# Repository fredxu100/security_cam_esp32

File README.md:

# Portable ESP32-CAM Security System
Low-cost, portable PIR-activated security device that detects motion, records video, and warns intruders.

**PROJECT FEATURES**
- Motion detection
- Camera capture/logging
- Local sound alarm
- Battery powered/portable

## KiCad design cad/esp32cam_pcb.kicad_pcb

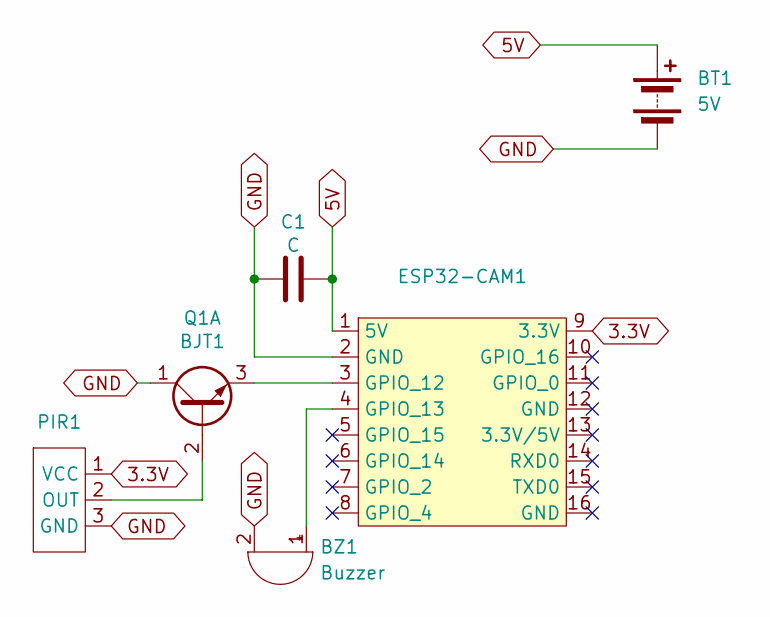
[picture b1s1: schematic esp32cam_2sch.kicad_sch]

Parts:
BT1: 5V; Banana_Jack_2Pin
BZ1: Buzzer; Buzzer_12x9.5RM7.6
C1: C; CP_Radial_D8.0mm_P3.50mm
ESP32-CAM1: ESP32_CAM
PIR1: PIR_SENSOR
Q1: BJT1; TO-92_Inline

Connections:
3.3V: ESP32-CAM1.9 (3.3V), PIR1.1 (VCC)
5V: BT1.1 (+), C1.2, ESP32-CAM1.1 (5V)
GND: BT1.2 (-), BZ1.2 (-), C1.1, ESP32-CAM1.2 (GND), PIR1.3 (GND), Q1.1 (C1)
unnamed: BZ1.1 (+), ESP32-CAM1.4 (GPIO_13)
unnamed: ESP32-CAM1.3 (GPIO_12), Q1.3 (E1)
unnamed: PIR1.2 (OUT), Q1.2 (B1)

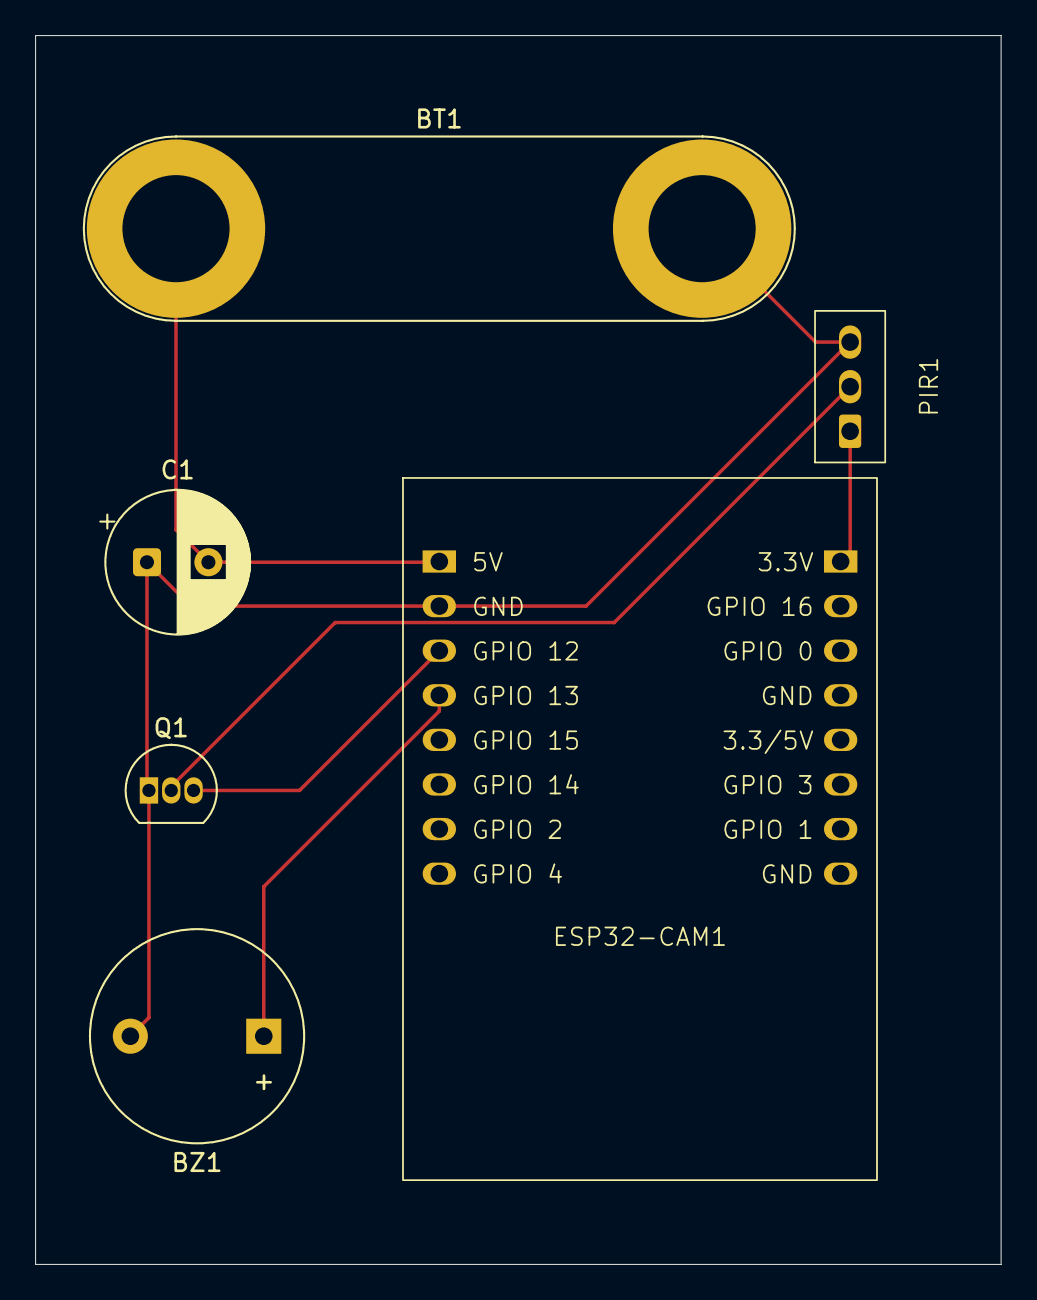
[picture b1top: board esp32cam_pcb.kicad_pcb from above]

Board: 2 copper layers, 55.0 x 70.0 mm, 6 parts (0 on the bottom side), 6 nets.

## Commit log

2025-11-29 Update README with project details and features
    Expanded project description and features in README.
2025-11-29 camera initialize
2025-12-07 camera v1 log
2025-12-19 Revise README to streamline project description
    Removed introductory text and updated project features.
2025-12-19 code/cad updates
2025-12-19 schematic images
2025-12-19 readme
2025-12-19 camera_demo
2025-12-19 motion demo
2025-12-19 camera demo
2025-12-19 breadboard
2025-12-19 Add hardware status update to README
2025-12-19 Revise README with demo information and notes
    Updated README to include demo details and hardware status.
2025-12-19 Update README formatting and section headers
2025-12-19 Update README formatting and content structure
2025-12-26 Rename README.txt to README.md
